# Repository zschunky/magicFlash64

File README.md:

# magicFlash64
## overview
The magicFlash64 is a kernal replacement for the Commodore 64 (no matter if PAL or NTSC). In total it offers 64 8KB slots (one slot has the size of one kernal) which can be used to store kernals, basic and programs. Writing slots can be done within the Commodore 64 by using a programmer application without the need to remove the Flash IC and program it on a external programmer. The magicFlash64 utilizes the flash memory AM29F040 and an Atmega48 micro controller. Originally it was planned to name the project easy kernal. Unfortunately it turned out this name was already used for a different C64 project and therefore project name magicFlash64 was born. On some PCBs you may still find the name easy kernal.
The build environment is based on gnu make Makefiles. Compiling and linking the firmware for the micro controller Atmega48 utilizes the avr-gcc compiler chain. Compiling and linking of C64 tools/kernals is based on the CC65 compiler chain. All syntax is based on these compiler chains.
## important notice for beta testers
Most critical is the communication between the microcontroller and the C64. The timing is heavily impacted by the PLA in use. Before trying to program slots please run the test program to ensure a proper working communication. In case the test program fails please do not attempt to update the firmware and program/erase any slots.

## downloads
Binary downloads can be found under releases.

## hardware
The current version of the hardware is 0.2.
 
### schematic

### the pcb
 
### part list
|ID|name|housing|amount|description|vendor|
|--|----------|-------|---------|-----------|-----------------|
|1|U3|PLCC32|1|AM29F040||
|2|C1|C_Disc_D3.4mm_W2.1mm_P2.50mm|1|100n||
|3|C2,C3|C_Disc_D3.4mm_W2.1mm_P2.50mm|2|22p||
|4|Y1|Crystal_HC18-U_Vertical|1|20MHz||
|5|J2|Pin_Header_Angled_1x07_Pitch2.54mm|1|1x7||
|6|JP1,JP2,JP3,JP5|Pin_Header_Straight_1x03_Pitch2.54mm|4|1x3||
|7|R1,R2|R_Axial_DIN0204_L3.6mm_D1.6mm_P2.54mm_Vertical|2|1k||
|8|R3,R4|R_Axial_DIN0204_L3.6mm_D1.6mm_P2.54mm_Vertical|2|10k||
|9|R5,R6,R7,R8|R_Axial_DIN0204_L3.6mm_D1.6mm_P2.54mm_Vertical|4|10K||
|10|D1,D2,D3,D4,D5,D6|D_DO-35_SOD27_P2.54mm_Vertical_AnodeUp|6|D||
|11|JP4|Pin_Header_Straight_1x02_Pitch2.54mm|1|1x2||
|12|U1|precision socket header|2|1x14||
|13|U2|DIP-28_W7.62mm|1|ATMEGA48-20PU||
|14|J4,J1|Pin_Header_Angeled_1x04_Pitch2.54mm|2|1x4||
|15|R10,R11|R_Axial_DIN0204_L3.6mm_D1.6mm_P2.54mm_Vertical|2|4.7K||
|16|C4|C_Disc_D3.4mm_W2.1mm_P2.50mm|1|220pF/1.2n||
|17|C5|C_Disc_D3.4mm_W2.1mm_P2.50mm|1|220p||
|18|R9,R12|R_Axial_DIN0204_L3.6mm_D1.6mm_P2.54mm_Vertical|2|100||
|19|R13|R_Axial_DIN0204_L3.6mm_D1.6mm_P2.54mm_Vertical|1|270||
|20|J3|Pin_Header_Angled_1x03_Pitch2.54mm|1|1x3||

### soldering the pcb
As first step the male headers for the pin socket should be soldered. For better access to solder the PLCC32 socket these male headers should be trimmed a bit on the solder side before soldering them. Use a socket or breadboard to ensure these header pins are straight. 

Please be careful soldering these pins because the PLCC32 pin are pretty close. Make sure to not solder them together (some of these neighbor pins are connected already but most are not). As next step the PLCC32 socket should be soldered. Please also be careful here while soldering to not generate a short to the header pins. Also double check the pin 1 position of the socket before soldering.

These 2 parts are the most critical parts to solder. The rest of the parts can soldered at any desired order. 

Please pay attention for the capacitor C4 selection of PCB v0.2 (see chapter known issues/capacitor C4).
### known issues
#### capacitor C4 (PCB v0.2 only)
The capacitor C4 needs to be selected depending on the target mainboard. For 250469 mainboards use 220pF and for all others use 1.2nF. There is also the possibility to solder a precision socket instead and plug in the correct capacitor.
#### labels for J1, J2, J3 and J4
When placing angeled headers the labels for J1, J2, J3 and J4 are no longer visible.
#### keyboard mounts on 250469 boards
When installing the magicFlash64 on a 250469 mainboard in C64C case which requires keyboards mounts this will be an issue because of clearance. 3D printed mounts can be used if the left mount will be shortend.
 
## modes of operation
The magicFlash64 can be used in 24 pin or 28 pin kernal sockets. Jumpers will need to be set correctly depending on the used pin socket. There are also 2 ways of usage: a full populated magicFlash64 or a partly populated magicFlash64. The full populated magicFlash64 offers the possibilty to write and control the magicFlash64 via software from the Commodore 64. The partly populated magicFlash64 relies on external control via header pins (eg connected to a keyman). Modifying content of the flash memory cannot be done in partly populated mode via the Commodore 64 and the flash memory needs to be removed and programmed externally.
### 24 pin kernal replacement
Supported Commodore 64 main boards are:
- KU14194HB (not tested)
- 326298 (not tested)
- 250407
- 250425
- 250466
- 251102 (SX-64, not tested)

Following jumper settings are required to be used as 24 pin kernal replacement:

While using the magicFlash64 on 24 pin socket the upper 2 pin rows will be outside of the socket (or shorter headers may be used during soldering).
### 28 pin kernal replacement
Supported Commodore 64 main boards are:
- 250469 (special keyboard mounts required for C64C cases with keyboard mounts)
- 310378 (C64 Rom of C128, not yet tested)

Following jumper settings are required to be used as 28 pin kernal replacement:

### partly populated magicFlash64
The partly populated magicFlash64 needs to be controlled from the outside via the J1 pin header. The flash content can only be modified by manual removing the flash IC and programming it with an external programmer. With this partly populated magicFlash64 the magicFlash64 may also be used in other platforms like floppy drives etc.
### header pins
The magicFlash64 offers a bunch of header pins which need to/can be connected to other signals. Some of them are mandatory and some are optional.

|connector|description|
|---------|--------------------------------------|
|J1|this header is used to connect the mandatory pins reset (pin1), restore (pin2), RW (pin3) to the C64 mainboard, gpio (pin4) was planned for future use but will be removed in future pcbs|
|J2|J2 is optional and can be used in 2 ways: in partly populated mode (no microcontroller attached) the slot will be selcted via this header, in full populated mode the header can be used to identify the current slot in use (eg overlay64)|
|J3|J3 is optional but highly recommended, J3 is used to connect the power LED of the C64 case|
|J4|J4 is not used yet and for future use, the idea behind is to provide an I2C bus to be able to connected a OLED LCD|

## preparing a C64 mainboard
In order to install a magicFlash64 on a  C64 mainboard several preparation need to be done. If the kernal ROM IC is soldered in it needs to be removed and a socket needs to be installed instead. In addition the magicFlash64 required 3 additional signals:
- restore key (available on keyboard connector pin 3)
- RW (available on any CIA pin 22)
- reset (available on any CIA pin 34)

Cables can be soldered right at these pins described above on the backside of the board or connected thru hole vias may be traced from these signals and used with male header instead. On such vias the solder needs to be removed via a desolder station or solder iron and desolder pump and then the male headers can be installed there. This allows the usage of dupont wires. These signal need to be connected to connector J1 (reset pin1, restore pin2, rw pin3)

On the connector J3 the power LED of the C64 should be plugged in. The empty slot of the plug should be placed at pin1 of J3.
 
## using the magicFlash64
When using the magicFlash64 it requires kernals to be programmed inside the FLASH memory otherwise the C64 will not boot up. In case the C64 is switched on and a blank screen is seen a bad kernal slot has been chose. You may hold the restore until it blinks and then release to select slot 63 (normally magicFlash64 menu).

The restore key can trigger some task by holding restore. While holding the first power LED will go off for 2s, then it will go back on for 2s, it will then blinks for 2s and afterwards go off again. When releasing the restore key while the LED is solid a C64 reset will trigged. When releasing the restore key while the LED blinks the kernal slot 63 will be selected and a reset will be executed.
## magicFlash64 menu
The magicFlash64 menu is a special kernal which allows you to select other kernals/carts and programs stored inside the flash of the magicFlash64. The kernal menu should be programmed in slot 63. It can be accessed in 2 ways:
- press the restore key down and hold it till the power LED blinks and release it while blinking
- press reset and hold it till the power LED blinks and release it

To navigate the magicFlash64 menu use the cursor keys or the joystick (joystick not yet implemented). Cursor up/down or joystick up/down will navigate between the slots. Cursor left/right or joystick left/right will navigate between kernal/prg/cart tab. The return key or fire button will select and execute the selected slot.
For fast jumping between slots type the slot number can be typed via the number keys (always 2 key strokes are required, for slot 1 type 01).

When selecting the prg tab and executing a prg with the RETURN key the kernal which was chosen in the kernal tab will be started and in case no cartidge was detected the prg will automatically started. In case a cartidge was detected the prg file will not be auomtatically started. You will need to push the restore key to initiate the starting of prg when the basic prompt has been reached.

The magicFlash64 menu also contains a lookup table about the used/free slots of the magicFlash64.

To upgrade the magicFlash64 menu you have to use the magicFlash64 programmer application. Select slot 63 and chose program (click p). A file selection will pop up and you need to select the magicFlash64 menu binary file. Then click t and set the type to menu. Now you will need to apply these changes by clicking f7.
## magicFlash64 programmer
The magicFlash64 programmer is application to erase and program the flash memory of the magicFlash64. When the application is started it will first check all 64 slots of the magicFlash64 to make sure empty slots are erased and programmed slots match to their crc.

After checking completed it will prompt you for a temporary storage device. Since the smallest erase size of the flash memory is 64 KByte (8 slots) it is requires some external storage to tempory save slots which shall not be erased. In addition a REU or GEORAM will buffer new loaded files and it will be faster when loading them into magicFlash64 (GEORAM via Ultimate 1541 II+ seems to have some issues, REU with Ultimate 1541 II+ works fine).

Finally you will enter the main screen of the magicFlash64 programmer application.
 
The selection screen is split into a few columns separated by "-":

|column       |description                                                                         |
|-------------|------------------------------------------------------------------------------------|
|1            |slot number                                                                         |
|2            |action to be done (E:erase, P:program, R:reprogram)                                 |
|3            |slot type (B:basic, K:kernal, E:empty, P:program, M:menu, C:cart, +:follow up slot) |
|4            |slot name                                                                           |

Following keyboard shortcuts are available:

|key(s)       |action                                                                              |
|-------------|------------------------------------------------------------------------------------|
|up/down      |navigate up/down                                                                    |
|0-9          |fast jumping to given slot (2 key strokes are required eg 01 for slot 1)            |
|p            |mark slot to be programmed, a popup for selecting a file will come up               |
|e            |mark slot to be erased                                                              |
|d            |set slot as default boot slot (when switching on the C64 this slot will be selected)|
|cbm-8/9/0/1  |select drive 8/9/10/11 as file operation (not backup drive)                         |
|t            |change slot type                                                                    |
|v            |view first 1000 byte of the slot on the screen (click space to exit)                |
|u            |undo all changes except set default                                                 |
|f7           |apply changes                                                                       |
|b            |boot slot imediately                                                                |

The action of the d key (set default) will be imediately. All other actions need to be applied via the f7 key.
Since slots have a fixed size of 8 KByte programm are carts may be bigger than 8 KByte. For this so called follow up slots are used.

Please also pay attention to slot 63. This slot is aimed to be the magicFlash64 menu. The magicFlash64 menu will also contain a table (directory) of all kernal slots. When modifiying any slot this slot table will be updated. Also when programming slot 63 the slot table will be patched in. Do not try to program a regular kernal into this slot because the slot table will break the kernal apart.

## internals
The following articles are intendet to give some technical background on how the magicFlash64 works and how to program it.
### the micro controller
The micro controller has only a few tasks:
- monitor the restore key to perform reset or select the magicFlash64 slot for the magicFlash64 menu
- monitor the reset pin and select the magicFlash64 slot for the magicFlash64 menu if reset is hold for more than 2s (the power LED will go off for the 1st 2s and blink)
- execute commands from the C64 to select a slot, generate the write enable signal to the flash, access the micro controller eeprom, access the micro controller RAM, set the LED, ...
- communicate to C64 in both directions

#### talking to the micro controller
The micro controller has 6 IOs connected to the address bus (A12,A11,A10,A9,A8,A0) and 1 IO to the output enable signal of the kernal ROM. This allows the micro controller to check each read a access to the kernal ROM. To generate an read access with only these few address bits following macro may be used:
```
.macro STEP value
  bit $e000|((value & $3e) << 7)|(value & 1)
.endmacro
```
The micro controller checks now for a magic sequence to start an command. The magic sequence is "$00,$2A,$15,$3f,cmd" and would be translated into following C64 macro:
```
.macro SEQ cmd
  STEP $00
  STEP $2A
  STEP $15
  STEP $3F
  STEP cmd
.endmacro
```
The order of these sequence must not be interrupted by any other access to the kernal ROM (interrupts should be disabled). Such opcodes cannot be executed from the KERNAL ROM since fetching opcodes would interrupt the sequence. Additional pre caution have to be taken to bad lines of the C64. In case any of the used opcodes wants to talk to the micro controller and will run into the 1st 3 cycles of the BA signal being pulled low the 6510 cpu will generated 3 times the same read access to the kernal ROM and this will corrupt the commincation to the micro controller. 
After the magic sequence was executed an additional read on the kernal ROM will be expected with the command on the address bus (A12,A11,A10,A9,A8,A0). Certain commands require additional data via reads on the kernal ROM. To generate such read with the content of accumulator value following macro code can be used:
```
.macro STEPA
  ldx #0
  lsr
  bcc :+
  inx
:
  stx tmp1
  ora #$e0
  sta tmp2
  ldy #0
  lda (tmp1),y
.endmacro
```
#### listening to the micro controller
The communication from the micro controller to the C64 differs to the communication towards the micro controller. For this communication the micro controller invokes restore key strokes. And the C64 needs to check for this. As initial start of such communication the C64 makes a read on the KERNAL ROM at $00 (A12,A11,A10,A9,A8,A0 eg: BIT $E000) and if there is nmi interrupt happing within n ms the bit was 1 otherwise 0. All reads are byte oriented so this bit read needs to be done 8 times including the inital start at read on the KERNAL ROM at $00. To read such values from the micro controller a proper command has to be executed before.
#### programming/erasing the flash
The micro controller has an IO connected to the write enable signal of the flash device. For programming/erasing the flash the micro controller generates the required write enable signal on the flash device. This will be done by following commands issue by the C64:
>cmdWrModeAutoSelect
cmdWrModeProgram
cmdWrModeErase
cmdWrModeReset

#### commands
##### cmdLed
##### cmdReset
##### cmdSelect
##### cmdWrModeAutoSelect
##### cmdWrModeProgram
##### cmdWrModeErase
##### cmdFwUpd
##### cmdSetDefault
##### cmdGetDefault
##### cmdGetSelected
##### cmdSetEeprom
##### cmdGetEeprom
##### cmdWrModeReset
##### cmdTest
##### cmdGetPrev
##### cmdSetRam
##### cmdGetRam
##### cmdGetVersion
##### cmdMcType

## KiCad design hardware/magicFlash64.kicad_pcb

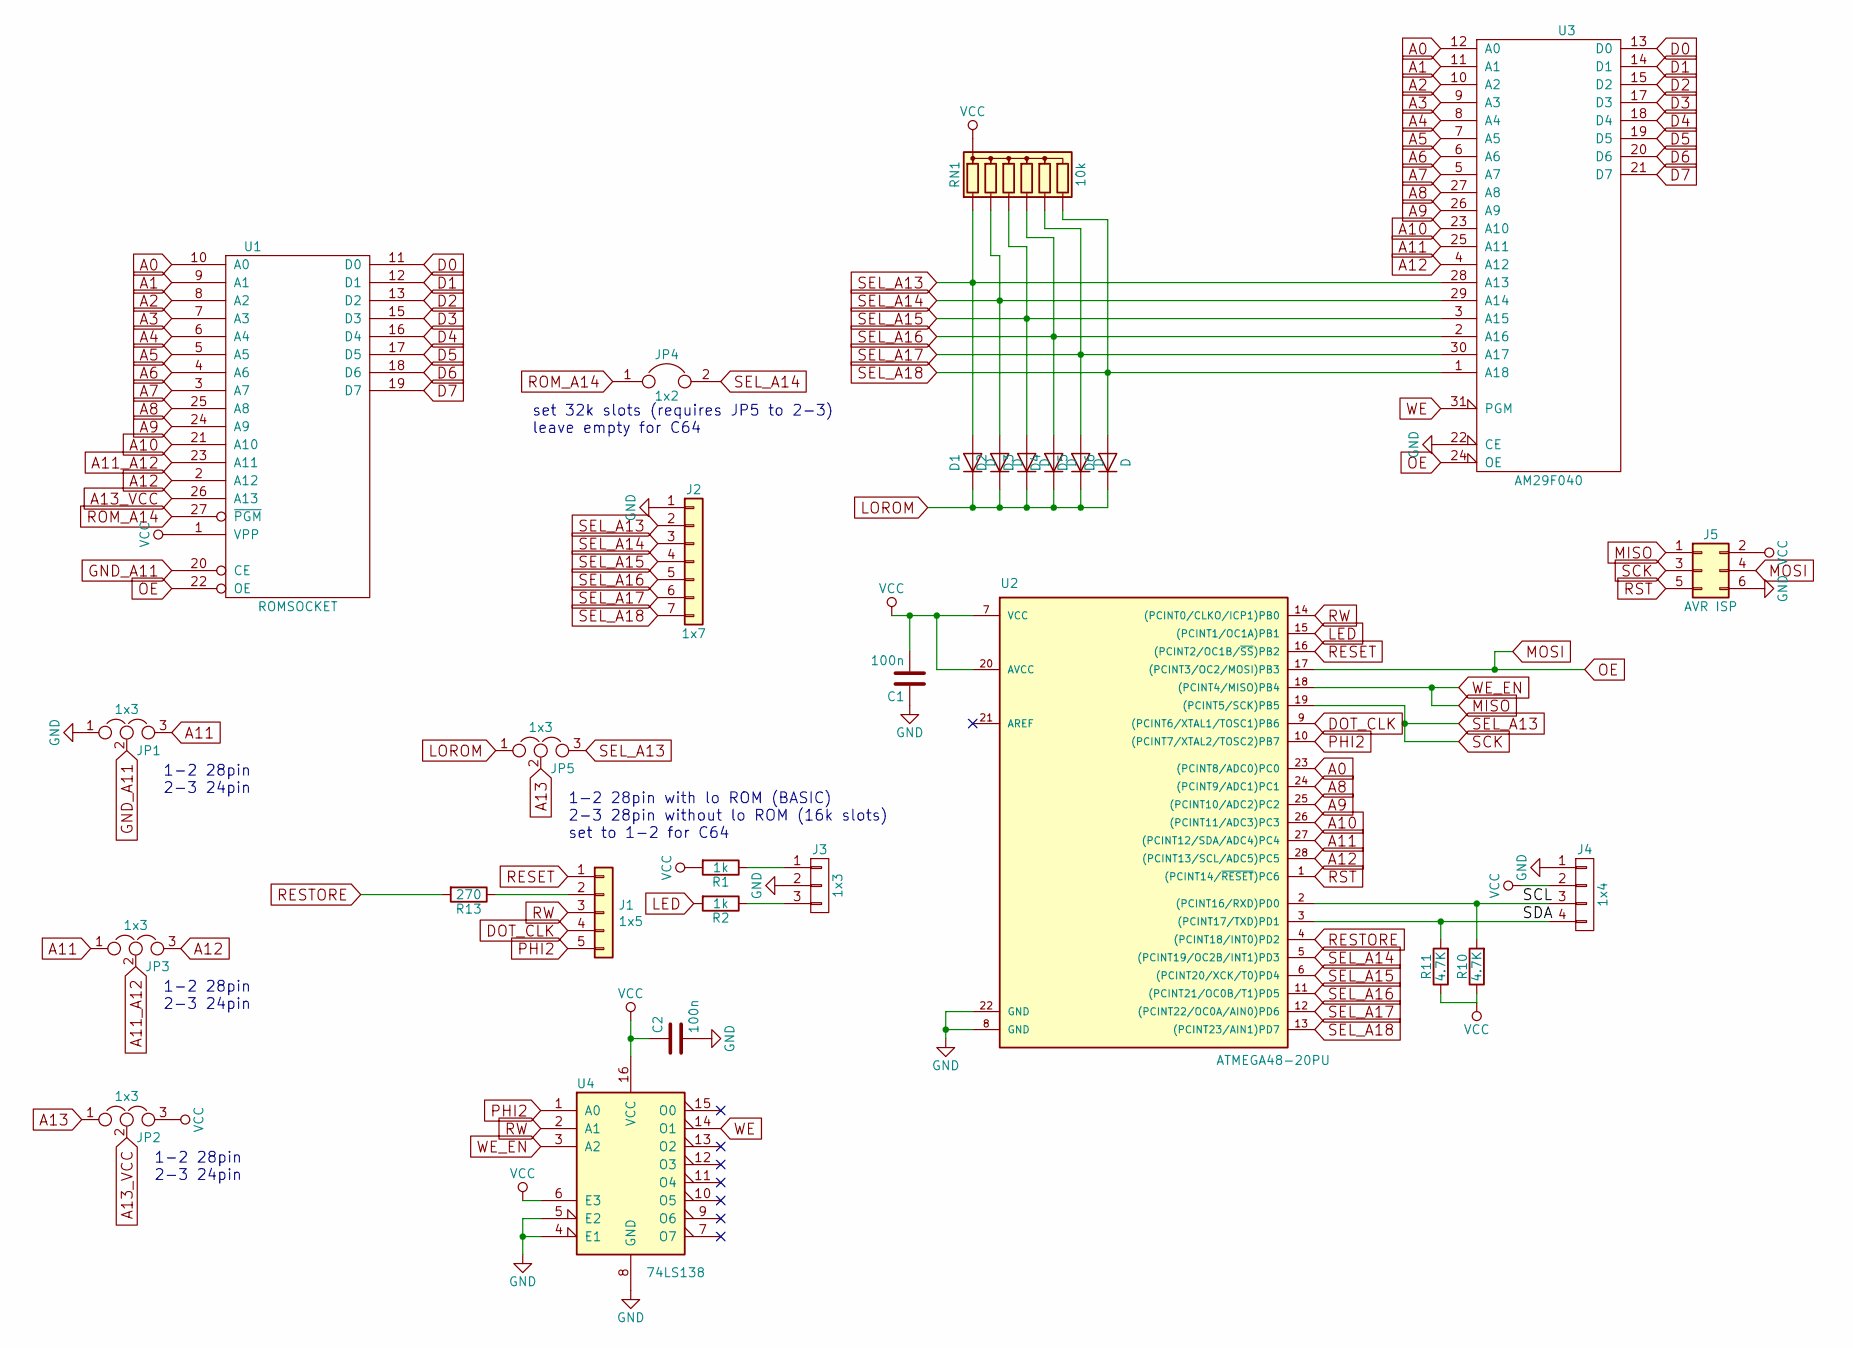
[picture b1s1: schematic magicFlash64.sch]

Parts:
C1, C2: 100n; C_Disc_D3.4mm_W2.1mm_P2.50mm
D1, D2, D3, D4, D5, D6: D; D_DO-35_SOD27_P2.54mm_Vertical_AnodeUp
J1: 1x5; Pin_Header_Straight_1x05_Pitch2.54mm
J2: 1x7; Pin_Header_Straight_1x07_Pitch2.54mm
J3: 1x3; Pin_Header_Straight_1x03_Pitch2.54mm
J4: 1x4; Pin_Header_Straight_1x04_Pitch2.54mm
J5: AVR ISP; Pin_Header_Straight_2x03_Pitch2.54mm
JP1, JP2, JP3, JP5: 1x3; Pin_Header_Straight_1x03_Pitch2.54mm
JP4: 1x2; Pin_Header_Straight_1x02_Pitch2.54mm
R1, R2: 1k; R_Axial_DIN0204_L3.6mm_D1.6mm_P2.54mm_Vertical
R10, R11: 4.7K; R_Axial_DIN0204_L3.6mm_D1.6mm_P2.54mm_Vertical
R13: 270; R_Axial_DIN0204_L3.6mm_D1.6mm_P2.54mm_Vertical
RN1: 10k; R_Array_SIP7
U1: ROMSOCKET; DIP-28_W15.24mm_Socket
U2: ATMEGA48-20PU; DIP-28_W7.62mm
U3: AM29F040; PLCC32
U4: 74LS138; DIP-16_W7.62mm_Socket

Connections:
/SCL: J4.3, R10.2, U2.2 ((PCINT16/RXD)PD0)
/SDA: J4.4, R11.2, U2.3 ((PCINT17/TXD)PD1)
A0: U1.10 (A0), U2.23 ((PCINT8/ADC0)PC0), U3.12 (A0)
A1: U1.9 (A1), U3.11 (A1)
A2: U1.8 (A2), U3.10 (A2)
A3: U1.7 (A3), U3.9 (A3)
A4: U1.6 (A4), U3.8 (A4)
A5: U1.5 (A5), U3.7 (A5)
A6: U1.4 (A6), U3.6 (A6)
A7: U1.3 (A7), U3.5 (A7)
A8: U1.25 (A8), U2.24 ((PCINT9/ADC1)PC1), U3.27 (A8)
A9: U1.24 (A9), U2.25 ((PCINT10/ADC2)PC2), U3.26 (A9)
A10: U1.21 (A10), U2.26 ((PCINT11/ADC3)PC3), U3.23 (A10)
A11: JP1.3, JP3.1, U2.27 ((PCINT12/SDA/ADC4)PC4), U3.25 (A11)
A11_A12: JP3.2, U1.23 (A11)
A12: JP3.3, U1.2 (A12), U2.28 ((PCINT13/SCL/ADC5)PC5), U3.4 (A12)
A13: JP2.1, JP5.2
A13_VCC: JP2.2, U1.26 (A13)
D0: U1.11 (D0), U3.13 (D0)
D1: U1.12 (D1), U3.14 (D1)
D2: U1.13 (D2), U3.15 (D2)
D3: U1.15 (D3), U3.17 (D3)
D4: U1.16 (D4), U3.18 (D4)
D5: U1.17 (D5), U3.19 (D5)
D6: U1.18 (D6), U3.20 (D6)
D7: U1.19 (D7), U3.21 (D7)
DOT_CLK: J1.4, U2.9 ((PCINT6/XTAL1/TOSC1)PB6)
GND: C1.1, C2.2, J2.1, J3.2, J4.1, J5.6, JP1.1, U1.14 (GND), U2.8 (GND), U2.22 (GND), U3.16 (GND), U3.22 (CE), U4.4 (E1), U4.5 (E2), U4.8 (GND)
GND_A11: JP1.2, U1.20 (CE)
LED: R2.2, U2.15 ((PCINT1/OC1A)PB1)
LOROM: D1.1 (K), D2.1 (K), D3.1 (K), D4.1 (K), D5.1 (K), D6.1 (K), JP5.1
MISO: J5.1, U2.18 ((PCINT4/MISO)PB4), U4.3 (A2)
MOSI: J5.4, U1.22 (OE), U2.17 ((PCINT3/OC2/MOSI)PB3), U3.24 (OE)
unnamed: J1.2, R13.1
unnamed: J3.1, R1.1
unnamed: J3.3, R2.1
PHI2: J1.5, U2.10 ((PCINT7/XTAL2/TOSC2)PB7), U4.1 (A0)
RESET: J1.1, U2.16 ((PCINT2/OC1B/~SS~)PB2)
RESTORE: R13.2, U2.4 ((PCINT18/INT0)PD2)
ROM_A14: JP4.1, U1.27 (~PGM)
RST: J5.5, U2.1 ((PCINT14/~RESET~)PC6)
RW: J1.3, U2.14 ((PCINT0/CLKO/ICP1)PB0), U4.2 (A1)
SCK: D1.2 (A), J2.2, J5.3, JP5.3, RN1.2 (R1), U2.19 ((PCINT5/SCK)PB5), U3.28 (A13)
SEL_A14: D2.2 (A), J2.3, JP4.2, RN1.3 (R2), U2.5 ((PCINT19/OC2B/INT1)PD3), U3.29 (A14)
SEL_A15: D3.2 (A), J2.4, RN1.4 (R3), U2.6 ((PCINT20/XCK/T0)PD4), U3.3 (A15)
SEL_A16: D4.2 (A), J2.5, RN1.5 (R4), U2.11 ((PCINT21/OC0B/T1)PD5), U3.2 (A16)
SEL_A17: D5.2 (A), J2.6, RN1.6 (R5), U2.12 ((PCINT22/OC0A/AIN0)PD6), U3.30 (A17)
SEL_A18: D6.2 (A), J2.7, RN1.7 (R6), U2.13 ((PCINT23/AIN1)PD7), U3.1 (A18)
VCC: C1.2, C2.1, J4.2, J5.2, JP2.3, R1.2, R10.1, R11.1, RN1.1 (common), U1.1 (VPP), U1.28 (VCC), U2.7 (VCC), U2.20 (AVCC), U3.32 (VCC), U4.6 (E3), U4.16 (VCC)
WE: U3.31 (PGM), U4.14 (O1)

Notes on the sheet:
1-2 28pin 2-3 24pin
1-2 28pin with lo ROM (BASIC) 2-3 28pin without lo ROM (16k slots) set to 1-2 for C64
set 32k slots (requires JP5 to 2-3) leave empty for C64

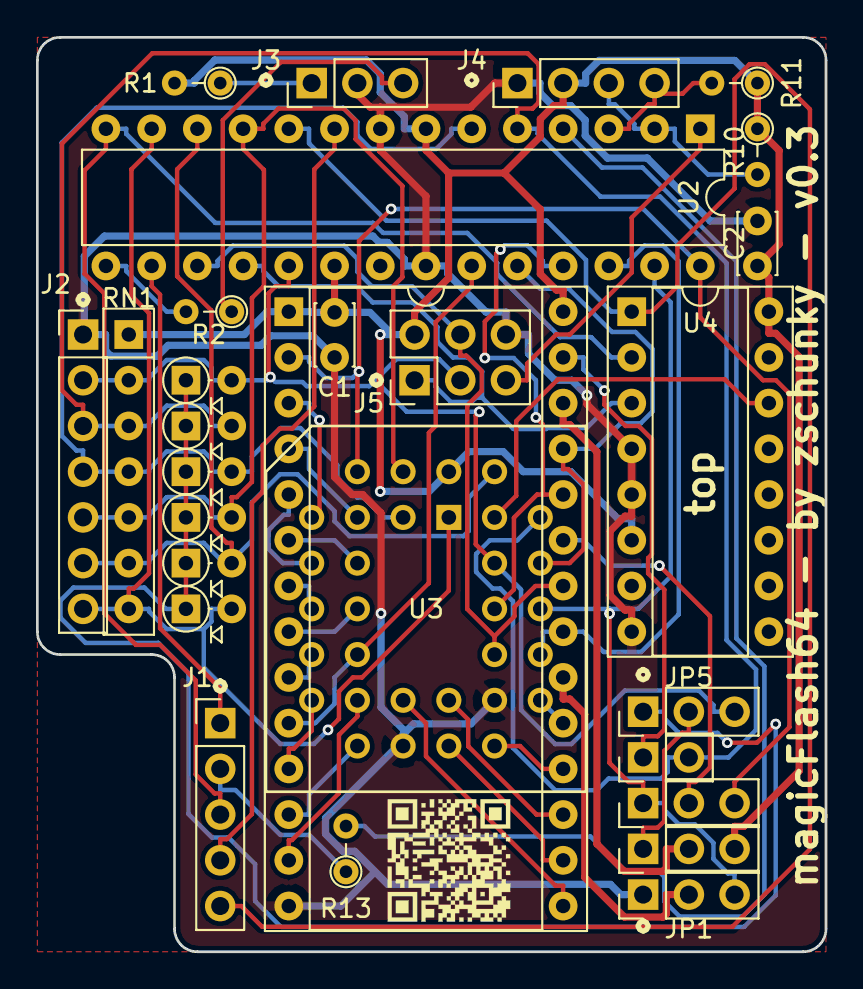
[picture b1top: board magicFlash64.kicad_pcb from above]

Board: 2 copper layers, 43.8 x 50.8 mm, 28 parts (0 on the bottom side), 50 nets.

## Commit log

2019-02-21 pcb version 0.2
2019-02-21 added .gitignore
2019-02-21 changed downloads in README
2019-02-22 added help to menu and qrcode to help in programmer & menu
2019-02-24 versions are now specified in makefile
2019-02-25 removed temp file
2019-02-25 add beta notice
2019-02-25 reworked test program
2019-02-25 Makefile generates now versions.txt file
2019-02-26 added tick (moving crsr while holding crsr key), fix memory overflow programmer, fix fast jump programmer
2019-02-27 added renaming of slots to programmer
2019-02-27 bugfix shifted screens
2019-02-27 added license header to some files
2019-03-02 added files to be ignored by git
2019-03-02 added header pin section to readme
2019-03-03 fixed typo
2019-03-05 fw v0.5, added support for spi isp, new high fuse:df instead of 7f, sel13 moved to new pin, old and new config supported with same fw (different fuses)
2019-03-06 fix prg start for basic prg
2019-03-10 bugfix led
2019-03-10 added software bootloader to atmega and recovery mode, to enable recovery mode short pin 1 and 3 of J4
2019-03-16 adapted fw to only accept timed magic sequence
2019-03-16 support for FC3 which holds nmi line low on reset
2019-04-13 added support of external clock via c64 dot clock
2019-04-13 added pcb v0.3 which uses external clock via c64 dot clock
2019-04-13 added a few more scope pictures
2019-04-13 added a view intermediate files to be ignored by git
2019-04-13 added reset+restore combo to select backup slot 55
2019-04-13 renamed ek api to mf64
2019-04-14 fix recovery address to page begin
2019-04-14 fix prg start at 20MHz Version
2019-04-14 removed debug signal on SCL
2019-04-14 adjusted versions
